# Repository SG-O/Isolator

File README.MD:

# Triple Isolator for two Step/Dir/En and one UART signal #

This was designed to be used with the [ODrive](https://github.com/madcowswe/ODrive "ODrive") motor controller. It may be useful for other things though.

## Documentation ##

You can find the manufacturing documentation [here.](https://github.com/SG-O/Isolator/tree/master/Doc)

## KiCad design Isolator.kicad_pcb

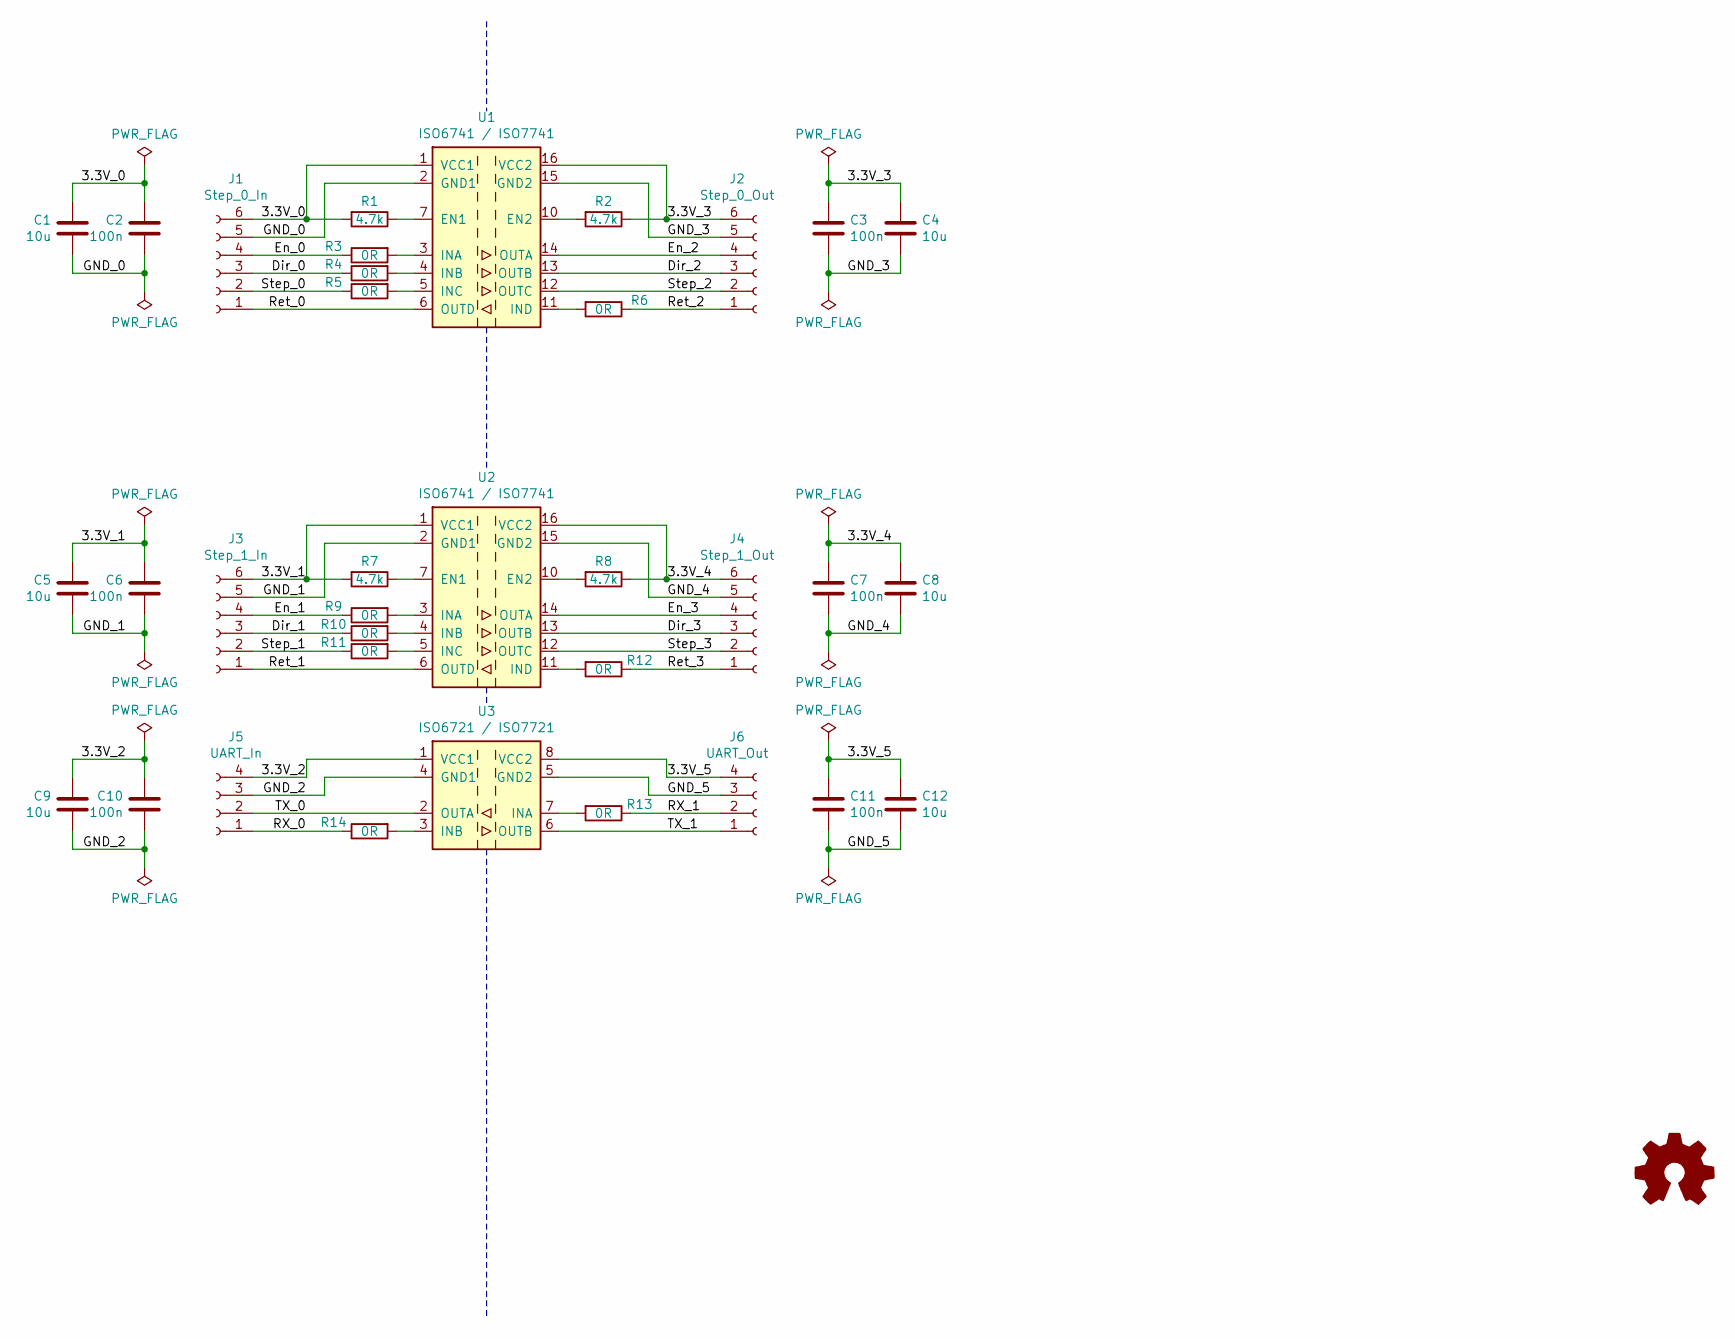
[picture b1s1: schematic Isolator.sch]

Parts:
C1, C4, C5, C8, C9, C12: 10u; R_1206_3216Metric; lcsc# C89632
C2, C3, C6, C7, C10, C11: 100n; C_0603_1608Metric; lcsc# C1591
J1: Step_0_In; PinSocket_1x06_P2.54mm_Vertical
J2: Step_0_Out; PinSocket_1x06_P2.54mm_Vertical
J3: Step_1_In; PinSocket_1x06_P2.54mm_Vertical
J4: Step_1_Out; PinSocket_1x06_P2.54mm_Vertical
J5: UART_In; PinSocket_1x04_P2.54mm_Vertical
J6: UART_Out; PinSocket_1x04_P2.54mm_Vertical
R1, R2, R7, R8: 4.7k; R_0603_1608Metric; lcsc# C23162
R3, R4, R5, R6, R9, R10, R11, R12, R13, R14: 0R; R_0603_1608Metric; lcsc# C21189
U1, U2: ISO6741 / ISO7741; SOIC-16W_7.5x10.3mm_P1.27mm
U3: ISO6721 / ISO7721; SOIC-8_3.9x4.9mm_P1.27mm

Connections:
/3.3V_0: C1.1, C2.1, J1.6, R1.2, U1.1 (VCC1)
/3.3V_1: C5.1, C6.1, J3.6, R7.2, U2.1 (VCC1)
/3.3V_2: C9.1, C10.1, J5.4, U3.1 (VCC1)
/3.3V_3: C3.1, C4.1, J2.6, R2.1, U1.16 (VCC2)
/3.3V_4: C7.1, C8.1, J4.6, R8.1, U2.16 (VCC2)
/3.3V_5: C11.1, C12.1, J6.4, U3.8 (VCC2)
/Dir_0: J1.3, R4.1
/Dir_1: J3.3, R10.1
/Dir_2: J2.3, U1.13 (OUTB)
/Dir_3: J4.3, U2.13 (OUTB)
/En_0: J1.4, R3.1
/En_1: J3.4, R9.1
/En_2: J2.4, U1.14 (OUTA)
/En_3: J4.4, U2.14 (OUTA)
/GND_0: C1.2, C2.2, J1.5, U1.2 (GND1), U1.8 (GND1)
/GND_1: C5.2, C6.2, J3.5, U2.2 (GND1), U2.8 (GND1)
/GND_2: C9.2, C10.2, J5.3, U3.4 (GND1)
/GND_3: C3.2, C4.2, J2.5, U1.9 (GND2), U1.15 (GND2)
/GND_4: C7.2, C8.2, J4.5, U2.9 (GND2), U2.15 (GND2)
/GND_5: C11.2, C12.2, J6.3, U3.5 (GND2)
/RX_0: J5.1, R14.1
/RX_1: J6.2, R13.1
/Ret_0: J1.1, U1.6 (OUTD)
/Ret_1: J3.1, U2.6 (OUTD)
/Ret_2: J2.1, R6.1
/Ret_3: J4.1, R12.1
/Step_0: J1.2, R5.1
/Step_1: J3.2, R11.1
/Step_2: J2.2, U1.12 (OUTC)
/Step_3: J4.2, U2.12 (OUTC)
/TX_0: J5.2, U3.2 (OUTA)
/TX_1: J6.1, U3.6 (OUTB)
unnamed: R1.1, U1.7 (EN1)
unnamed: R2.2, U1.10 (EN2)
unnamed: R3.2, U1.3 (INA)
unnamed: R4.2, U1.4 (INB)
unnamed: R5.2, U1.5 (INC)
unnamed: R6.2, U1.11 (IND)
unnamed: R7.1, U2.7 (EN1)
unnamed: R8.2, U2.10 (EN2)
unnamed: R9.2, U2.3 (INA)
unnamed: R10.2, U2.4 (INB)
unnamed: R11.2, U2.5 (INC)
unnamed: R12.2, U2.11 (IND)
unnamed: R13.2, U3.7 (INA)
unnamed: R14.2, U3.3 (INB)

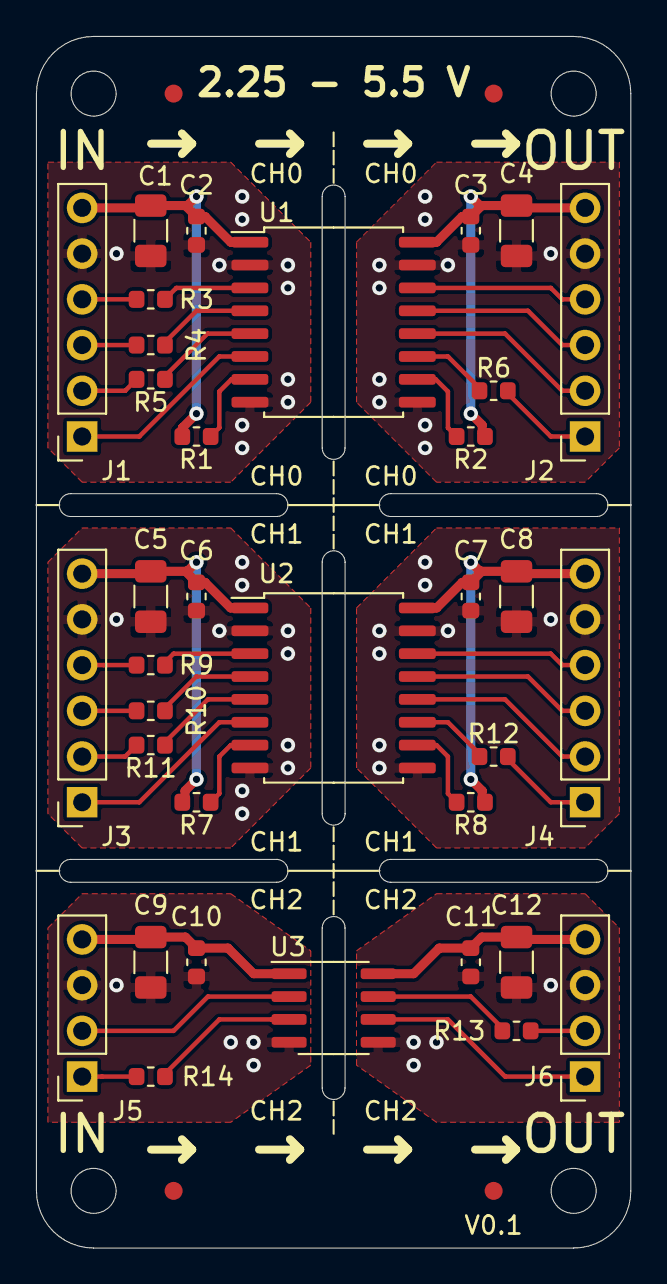
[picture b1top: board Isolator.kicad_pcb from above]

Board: 2 copper layers, 33.0 x 67.3 mm, 43 parts (0 on the bottom side), 46 nets.

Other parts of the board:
 : Fiducial_1mm_Dia_2mm_Outer
 #2,  #3,  #4: Fiducial_1mm_Dia_2mm_Outer
 #5,  #6,  #7,  #8: MountingHole_2.5mm

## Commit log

2020-09-23 Added mounting holes. (They got lost somehow)
2020-09-23 Create LICENSE
2020-09-23 Added panelized version
2020-09-23 Added fiducials to single board
2020-09-23 Added BOM
2020-09-23 Added board images for the panel
2020-09-23 Added dimensional drawing
2020-09-23 Added more documentation
2020-09-23 Added documentation section to main README
2020-10-01 Switched RX and TX silkscreen
2020-10-26 Fixed typo
